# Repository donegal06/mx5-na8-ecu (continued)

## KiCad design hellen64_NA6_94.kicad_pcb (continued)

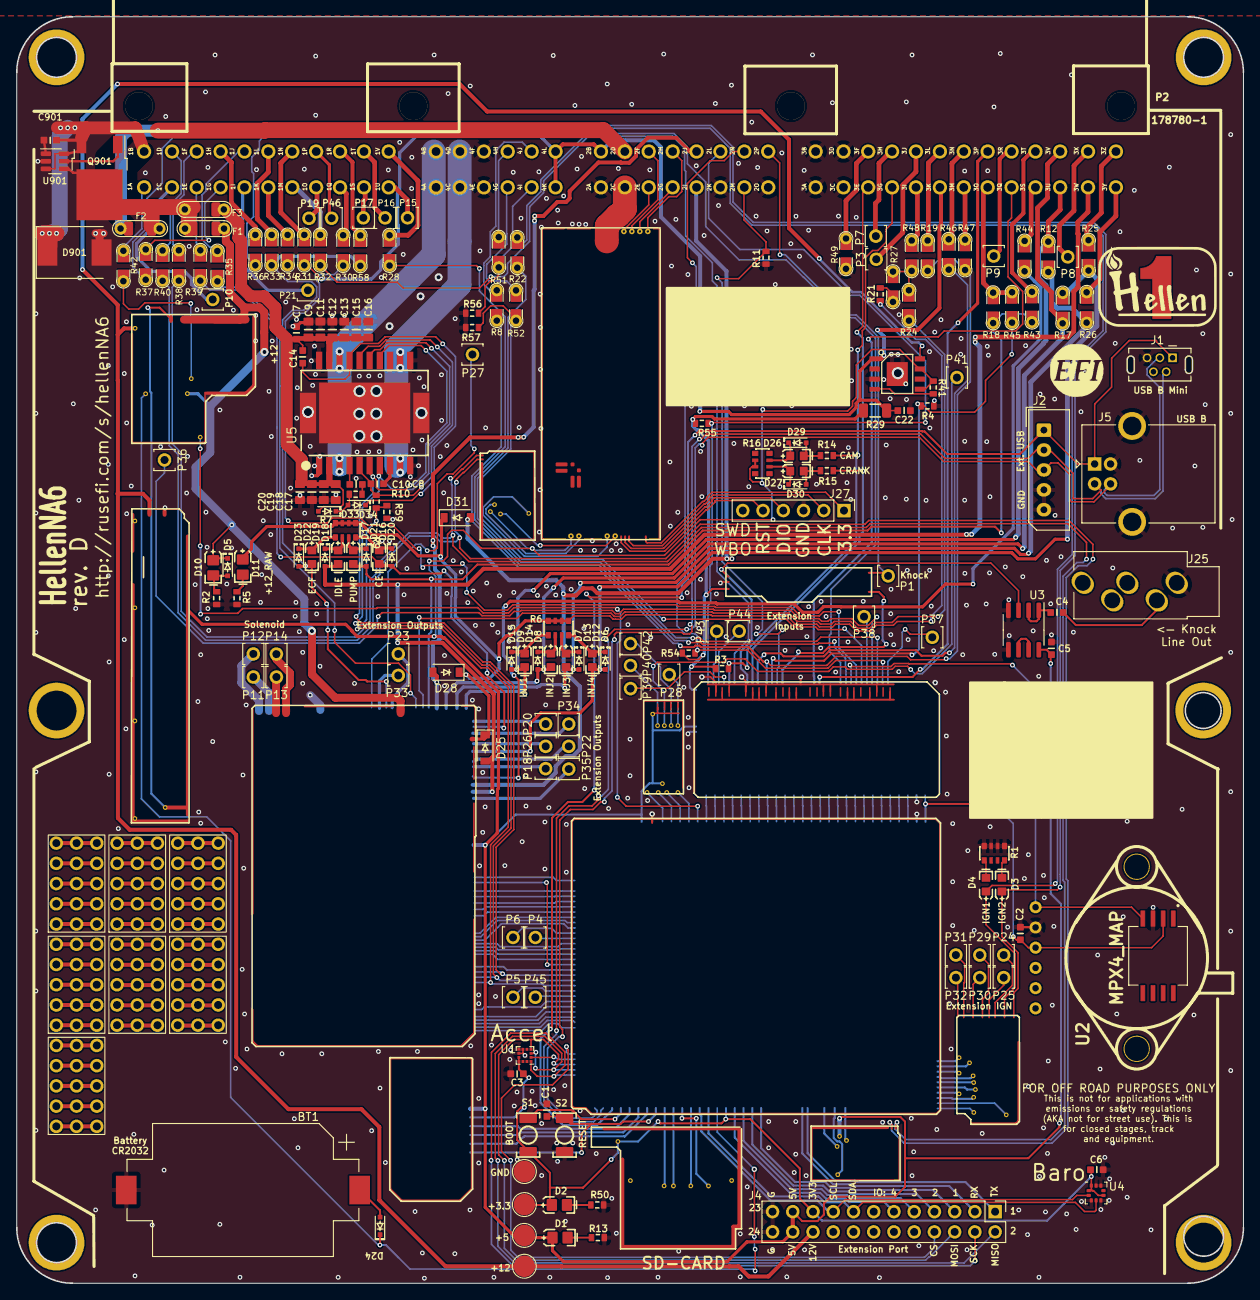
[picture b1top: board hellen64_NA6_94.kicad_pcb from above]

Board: 2 copper layers, 154.0 x 159.0 mm, 213 parts (1 on the bottom side), 295 nets.

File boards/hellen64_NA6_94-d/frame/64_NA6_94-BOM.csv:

Comment,Designator,Footprint,LCSC Part #
"BATTERY_CR2032","BT1","BATTERY-2032","C70377"
"100n","C1","C0603","C14663"
"100n","C2","C0603","C14663"
"100n","C3","C0603","C14663"
"10u","C4","C0603","C19702"
"100n","C5","C0603","C14663"
"100n","C6","C0603","C14663"
"100n","C7","C0603","C14663"
"6.8n","C8","C0603","C1631"
"10u","C9","C0805","C15850"
"10n","C10","C0603","C57112"
"10u","C11","C0805","C15850"
"10u","C12","C0805","C15850"
"10u","C13","C0805","C15850"
"220n","C14","C0603","C21120"
"10u","C15","C0805","C15850"
"10u","C16","C0805","C15850"
"10u","C17","C0805","C15850"
"10u","C18","C0805","C15850"
"10u","C19","C0805","C15850"
"10u","C20","C0805","C15850"
"1u","C22","C0603","C15849"
"100n","C901","C0603","C14663"
"LED-GREEN-0805","D1","LED-0805","C2297"
"LED-GREEN-0805","D2","LED-0805","C2297"
"LED-BLUE-0603","D3","LED-0603","C72041"
"LED-BLUE-0603","D4","LED-0603","C72041"
"1N4148WS","D5","SOD-323","C2128"
"LED-RED-0603","D6","LED-0603","C2286"
"LED-RED-0603","D7","LED-0603","C2286"
"LED-RED-0603","D8","LED-0603","C2286"
"LED-RED-0603","D9","LED-0603","C2286"
"LED-GREEN-0805","D10","LED-0805","C2297"
"LED-GREEN-0805","D11","LED-0805","C2297"
"1N4148WS","D12","SOD-323","C2128"
"1N4148WS","D13","SOD-323","C2128"
"1N4148WS","D14","SOD-323","C2128"
"1N4148WS","D15","SOD-323","C2128"
"LED-WHITE-0603","D16","LED-0603","C2290"
"LED-WHITE-0603","D17","LED-0603","C2290"
"LED-WHITE-0603","D18","LED-0603","C2290"
"LED-WHITE-0603","D19","LED-0603","C2290"
"1N4148WS","D20","SOD-323","C2128"
"1N4148WS","D21","SOD-323","C2128"
"1N4148WS","D22","SOD-323","C2128"
"1N4148WS","D23","SOD-323","C2128"
"1N4148WS","D24","SOD-323","C2128"
"B5819W","D25","SOD-123","C8598"
"LED-WHITE-0603","D26","LED-0603","C2290"
"LED-WHITE-0603","D27","LED-0603","C2290"
"B5819W","D28","SOD-123","C8598"
"1N4148WS","D29","SOD-323","C2128"
"1N4148WS","D30","SOD-323","C2128"
"B5819W","D31","SOD-123","C8598"
"1N4148WS","D33","SOD-323","C2128"
"1N4148WS","D34","SOD-323","C2128"
"SMCJ33CA","D901","D_SMC","C699040"
"Fuse-Pad-Pad","F1","PAD-1206-PAD","C182446"
"Fuse-Pad-Pad","F2","PAD-1206-PAD","C182446"
"Fuse-Pad-Pad","F3","PAD-1206-PAD","C182446"
"LOGO","G1","LOGO",""
"DISCLAIMER","G2","Off_Road_Disclaimer",""
"LOGO","G3","LOGO",""
"PROTO_AREA","G4","PROTO_AREA",""
"PROTO_AREA","G5","PROTO_AREA",""
"PROTO_AREA","G6","PROTO_AREA",""
"PROTO_AREA","G7","PROTO_AREA",""
"PROTO_AREA","G9","PROTO_AREA",""
"PROTO_AREA","G11","PROTO_AREA",""
"PROTO_AREA","G12","PROTO_AREA",""
"USB_B_Mini","J1","USB-MINI-B-VERTICAL","C13453"
"Conn_01x05_Male","J2","Molex_SPOX_5267-05A_1x05_P2.50mm_Vertical",""
"Conn_02x12_Odd_Even","J4","PinHeader_2x12_P2.54mm_Vertical",""
"USB_B","J5","USB_B","C46392"
"Conn_01x01","J11","MountingHole_4.5mm_Pad",""
"Conn_01x01","J13","MountingHole_4.5mm_Pad",""
"Conn_01x01","J14","MountingHole_4.5mm_Pad",""
"Conn_01x01","J15","MountingHole_4.5mm_Pad",""
"Conn_01x01","J16","MountingHole_4.5mm_Pad",""
"Conn_01x01","J17","MountingHole_4.5mm_Pad",""
"Conn_01x01","J19","TestPoint_Pad_D2.0mm",""
"Conn_01x01","J20","TestPoint_Pad_D2.0mm",""
"Conn_01x01","J21","TestPoint_Pad_D2.0mm",""
"Conn_01x01","J22","TestPoint_Pad_D2.0mm",""
"Conn_01x01","J24","TestPoint_Pad_D2.0mm",""
"AudioJack3_SwitchTR","J25","Jack_3.5mm_PJ-3250-5A","C165947"
"Conn_01x06","J27","PinHeader_1x06_P2.54mm_Vertical",""
"Module:input/0.1","M1","input",""
"Module:ign8/0.2","M2","ign8",""
"Module:mcu144/0.6","M3","mcu",""
"Module:sd/0.1","M4","sd",""
"Module:output/0.3","M5","output",""
"Module:dinput4/0.1","M6","dinput4",""
"Module:stlink/0.1","M7","stlink",""
"Module:can/0.1","M8","can",""
"Module:knock/0.1","M9","knock",""
"Module:power12/0.2","M10","power12",""
"Module:power5/0.2","M11","power5",""
"Module:wbo/0.3","M12","wbo",""
"Module:can/0.1","M13","can",""
"Pad","P1","PAD-TH",""
"178780-1","P2","178780-1",""
"Pad","P3","PAD-TH",""
"Pad","P4","PAD-TH",""
"Pad","P5","PAD-TH",""
"Pad","P6","PAD-TH",""
"Pad","P7","PAD-TH",""
"Pad","P8","PAD-TH",""
"Pad","P9","PAD-TH",""
"Pad","P10","PAD-TH",""
"Pad","P11","PAD-TH",""
"Pad","P12","PAD-TH",""
"Pad","P13","PAD-TH",""
"Pad","P14","PAD-TH",""
"Pad","P15","PAD-TH",""
"Pad","P16","PAD-TH",""
"Pad","P17","PAD-TH",""
"Pad","P18","PAD-TH",""
"Pad","P19","PAD-TH",""
"Pad","P20","PAD-TH",""
"Pad","P21","PAD-TH",""
"Pad","P22","PAD-TH",""
"Pad","P23","PAD-TH",""
"Pad","P24","PAD-TH",""
"Pad","P25","PAD-TH",""
"Pad","P26","PAD-TH",""
"Pad","P27","PAD-TH",""
"Pad","P28","PAD-TH",""
"Pad","P29","PAD-TH",""
"Pad","P30","PAD-TH",""
"Pad","P31","PAD-TH",""
"Pad","P32","PAD-TH",""
"Pad","P33","PAD-TH",""
"Pad","P34","PAD-TH",""
"Pad","P35","PAD-TH",""
"Pad","P36","PAD-TH",""
"Pad","P37","PAD-TH",""
"Pad","P38","PAD-TH",""
"Pad","P39","PAD-TH",""
"Pad","P40","PAD-TH",""
"Pad","P41","PAD-TH",""
"Pad","P42","PAD-TH",""
"Pad","P43","PAD-TH",""
"Pad","P44","PAD-TH",""
"Pad","P45","PAD-TH",""
"Pad","P46","PAD-TH",""
"NCEP078N10AK","Q901","DPAK","C2686699"
"470","R1","R0603-4","C25510"
"5.1k","R2","R0603","C23186"
"4.7k","R3","R0603","C23162"
"1k","R4","R0603","C21190"
"5.1k","R5","R0603","C23186"
"4.7k","R6","R0603-4","C1980"
"20k","R7","R0603-4","C12004"
"Jumper-Pad-Pad","R8","PAD-0805-PAD"," C17477"
"100k","R9","R0603","C25803"
"100","R10","R0603","C22775"
"680k","R11","R0603","C25822"
"Jumper-Pad-Pad","R12","PAD-0805-PAD","C17477"
"1.6k","R13","R0603","C22847"
"0","R14","R0603","C21189"
"0","R15","R0603","C21189"
"4.7k","R16","R0603-4","C1980"
"Jumper-Pad-Pad","R17","PAD-0805-PAD","C17477"
"Jumper-Pad-Pad","R18","PAD-0805-PAD"," C17477"
"Jumper-Pad-Pad","R19","PAD-0805-PAD","C17477"
"1k","R21","R0603","C21190"
"Jumper-Pad-Pad","R22","PAD-0805-PAD"," C17477"
"Jumper-Pad-Pad","R24","PAD-0805-PAD"," C17477"
"Jumper-Pad-Pad","R25","PAD-0805-PAD"," C17477"
"Jumper-Pad-Pad","R26","PAD-0805-PAD"," C17477"
"Jumper-Pad-Pad","R27","PAD-0805-PAD"," C17477"
"Jumper-Pad-Pad","R28","PAD-0805-PAD"," C17477"
"SMD1206B035TF/16","R29","R1206","C269114"
"Jumper-Pad-Pad","R30","PAD-0805-PAD"," C17477"
"Jumper-Pad-Pad","R31","PAD-0805-PAD"," C17477"
"Jumper-Pad-Pad","R32","PAD-0805-PAD"," C17477"
"Jumper-Pad-Pad","R33","PAD-0805-PAD"," C17477"
"Jumper-Pad-Pad","R34","PAD-0805-PAD"," C17477"
"Jumper-Pad-Pad","R35","PAD-0805-PAD"," C17477"
"Jumper-Pad-Pad","R36","PAD-0805-PAD"," C17477"
"Jumper-Pad-Pad","R37","PAD-0805-PAD"," C17477"
"Jumper-Pad-Pad","R38","PAD-0805-PAD"," C17477"
"Jumper-Pad-Pad","R39","PAD-0805-PAD"," C17477"
"Jumper-Pad-Pad","R40","PAD-0805-PAD"," C17477"
"4.7k","R41","R0603","C23162"
"Jumper-Pad-Pad","R42","PAD-0805-PAD"," C17477"
"Jumper-Pad-Pad","R43","PAD-0805-PAD"," C17477"
"Jumper-Pad-Pad","R44","PAD-0805-PAD"," C17477"
"Jumper-Pad-Pad","R45","PAD-0805-PAD","C17477"
"Jumper-Pad-Pad","R46","PAD-0805-PAD"," C17477"
"Jumper-Pad-Pad","R47","PAD-0805-PAD"," C17477"
"Jumper-Pad-Pad","R48","PAD-0805-PAD"," C17477"
"Jumper-Pad-Pad","R49","PAD-0805-PAD"," C17477"
"750","R50","R0603","C23241"
"Jumper-Pad-Pad","R51","PAD-0805-PAD"," C17477"
"Jumper-Pad-Pad","R52","PAD-0805-PAD"," C17477"
"2.7k","R54","R0603","C13167"
"2.7k","R55","R0603","C13167"
"680k","R56","R0603","C25822"
"680k","R57","R0603","C25822"
"Jumper-Pad-Pad","R58","PAD-0805-PAD","C17477"
"10k","R59","R0603","C25804"
"Button_SPST","S1","SMD-2_2.9x3.9x1.7","C115357"
"Button_SPST","S2","SMD-2_2.9x3.9x1.7","C115357"
"LIS2DW12TR","U1","LGA-12_2x2mm_P0.5mm","C189624"
"MPX4_MAP","U2","MPX-4_MAP",""
"MCP6002-xSN","U3","SO8","C7377"
"LPS25HB","U4","HLGA-10","C87898"
"L6205PD","U5","SO20POWER","C36543"
"TLS115","U6","PG-DSO-8-43","C540242"
"MPXH6400A","U7","MPXH6400A-SSOP8","C511770"
"LM74700QDBVRQ1","U901","SOT23-6","C2941042"
